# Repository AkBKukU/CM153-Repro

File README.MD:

# Philips CM-153 LMSI Reproduction Card

This project aims to reproduce the LMSI CM-153 card needed to operate a Philips CM-100 CD-ROM drive. This drive was originally released in 1985 and used an early version of the LSMI protocol to connect. Later versions of LMSI cards, such as the CM-260, are not compatible with earlier drives (I do not know what the exact compatibilities are). So an early card is required. The CM-153 is a very uncommon part to find due to it's limited use, high cost, and the fact that it would probably be tossed out with the computer when upgraded being separated from its original drive.

Thanks to Roland who has a [working CM-100 and CM-153](https://www.youtube.com/watch?v=fj-uSWg0LOY) we have some pretty high quality reference images of what this card looks like. It uses all off the shelf 74 series logic chips and one 8251A UART controller. It should therefore be possible to recreate without needing any rare chips or ROM dumps.

## Current Status

The card has been fully reverse engineered and tested to be functional. It has been demonstrated to work using [this](http://mpolibbs.steptail.com/hardware/CDROM/PHILIPS/CM50DRV.ZIP) driver with a CM100 drive.

## Notes

A more acurate build will put 7121 in a socket as it must be removed to use the card with an internal drive. If you just want to use it with an external drive this can be ommited.

The selected DB-15 connector doesn't include the screw nuts which can be purchased separately.

## Parts List

*(Parts picked on 2022-09-07 and reflected best available stock)*

|RefDes|Original Part Number| Datasheet| Digikey Part| Mouser Part|
--- | --- | ---| ---| ---|
|7101|PC74HCT245P|[Datasheet](https://assets.nexperia.com/documents/data-sheet/74HC_HCT245.pdf)|[CD74HCT245E](https://www.digikey.com/en/products/detail/texas-instruments/CD74HCT245E/38454)|[SN74HCT245NE4](https://www.mouser.com/ProductDetail/Texas-Instruments/SN74HCT245NE4?qs=SL3LIuy2dWzrNeCJprt44g%3D%3D)|
|7102|PC74HCT244P|[Datasheet](https://assets.nexperia.com/documents/data-sheet/74HC_HCT244.pdf)|[CD74HCT244E](https://www.digikey.com/en/products/detail/texas-instruments/CD74HCT244E/38450)|[CD74HCT244E](https://www.mouser.com/ProductDetail/Texas-Instruments/CD74HCT244E?qs=Zu35EjizYSQlHH5t78bA9Q%3D%3D)|
|7104,7105|PC74HCT138P|[Datasheet](https://archive.org/details/74HCT138)|[CD74HCT138E](https://www.digikey.com/en/products/detail/texas-instruments/CD74HCT138E/38262)|[CD74HCT138E](https://www.mouser.com/ProductDetail/Texas-Instruments/CD74HCT138E?qs=IEl3ej0IqwCH%2FZM9hy22Dg%3D%3D)|
|7106|PC74HC08P|[Datasheet](https://archive.org/details/manuallib-id-2654066)|[TC74HC08APF](https://www.digikey.com/en/products/detail/toshiba-semiconductor-and-storage/TC74HC08APF/870461)|[SN74HC08AN](https://www.mouser.com/ProductDetail/Texas-Instruments/SN74HC08AN?qs=byeeYqUIh0O9MyGywGYg%252Bw%3D%3D)|
|7107,7108|PC74HC32P|[Datasheet](https://assets.nexperia.com/documents/data-sheet/74HC_HCT32.pdf)|**!M!**[NTE74HC32](https://www.digikey.com/en/products/detail/nte-electronics-inc/NTE74HC32/11650138)|[SN74HC32N](https://www.mouser.com/ProductDetail/Texas-Instruments/SN74HC32N?qs=tJ5HNKWh3OWs99bm2e8RtQ%3D%3D)|
|7109|PC74HC368P|[Datasheet](https://assets.nexperia.com/documents/data-sheet/74HC_HCT368.pdf)|[SN74HC368N](https://www.digikey.com/en/products/detail/texas-instruments/SN74HC368N/376786)|[SN74HC368N](https://www.mouser.com/ProductDetail/Texas-Instruments/SN74HC368N?qs=7KMwW2o1%252BmQFMEJMMaje4Q%3D%3D)|
|7110|PC74HC04P|[Datasheet](https://assets.nexperia.com/documents/data-sheet/74HC_HCT04.pdf)|[SN74HC04N](https://www.digikey.com/en/products/detail/texas-instruments/SN74HC04N/277212)|[SN74HC04AN](https://www.mouser.com/ProductDetail/Texas-Instruments/SN74HC04AN?qs=byeeYqUIh0N6S9uYkR6RCw%3D%3D)|
|7111|PC74HC125P|[Datasheet](https://assets.nexperia.com/documents/data-sheet/74HC_HCT125.pdf)|[CD74HC125E](https://www.digikey.com/en/products/detail/texas-instruments/CD74HC125E/475901)|[SN74HC125NE4](https://www.mouser.com/ProductDetail/Texas-Instruments/SN74HC125NE4?qs=AgY10sKTvDLokkOrwnzHmA%3D%3D)|
|7112,7113|PC74HC74P|[Datasheet](https://assets.nexperia.com/documents/data-sheet/74HC_HCT74.pdf)|NOT AVAILABLE|[CD74HC74EE4](https://www.mouser.com/ProductDetail/Texas-Instruments/CD74HC74EE4?qs=xFfolx0DHx2A6AZK2ZbvuQ%3D%3D)|
|7114,7115|PC74HC4024P|[Datasheet](https://assets.nexperia.com/documents/data-sheet/74HC4024.pdf)|[CD74HC4024E](https://www.digikey.com/en/products/detail/texas-instruments/CD74HC4024E/376737)|[CD74HC4024E](https://www.mouser.com/ProductDetail/Texas-Instruments/CD74HC4024E?qs=pt%2FIv5r0EPeVxf9RvRS8Kg%3D%3D)|
|7116,7117,7118|MC74HC595AN|[Datasheet](https://assets.nexperia.com/documents/data-sheet/74HC_HCT595.pdf)|[CD74HC595E](https://www.digikey.com/en/products/detail/texas-instruments/CD74HC595E/1507396)|[SN74HC595NE4](https://www.mouser.com/ProductDetail/Texas-Instruments/SN74HC595NE4?qs=AgY10sKTvDK0jki9CKjSwg%3D%3D)|
|7119|P8251A|[Datasheet](http://map.grauw.nl/resources/midi/intel_8251.pdf)|NOT AVAILABLE|NOT AVAILABLE|
|7120|DS26LS31CN|[Datasheet](https://www.ti.com/lit/ds/symlink/am26ls31.pdf)|NOT AVAILABLE|[AM26LS31CN](https://www.mouser.com/ProductDetail/Texas-Instruments/AM26LS31CN?qs=mTHRaKC2c7NO%252BlWH6D4lHg%3D%3D)|
|7121|DS26LS32CN|[Datasheet](https://www.ti.com/lit/ds/symlink/am26ls32am.pdf)|[AM26LS32ACN](https://www.digikey.com/en/products/detail/texas-instruments/AM26LS32ACN/277026)|[AM26LS32ACN](https://www.mouser.com/ProductDetail/Texas-Instruments/AM26LS32ACN?qs=IF4wzcbwb3oK65Lb3k1iHg%3D%3D)|
|X-TAL|4.9152MHz||[MP042](https://www.digikey.com/en/products/detail/cts-frequency-controls/MP042/67676)|[MP042](https://www.mouser.com/ProductDetail/CTS-Electronic-Components/MP042?qs=Mr%252BgrRYddfqYTabPpjTZhQ%3D%3D)|
|Big cap (C9)|50V 10uF||[ECA-1HHG100B](https://www.digikey.com/en/products/detail/panasonic-electronic-components/ECA-1HHG100B/413608)|[ECA-1HHG100B](https://www.mouser.com/ProductDetail/Panasonic/ECA-1HHG100B?qs=86KMePBwEH3eLbQCzM6gng%3D%3D)|
|X5|2x8 pin IDC||2x [826656-2](https://www.digikey.com/en/products/detail/te-connectivity-amp-connectors/826656-2/2276228)|2x [826656-2](https://www.mouser.com/ProductDetail/TE-Connectivity/826656-2?qs=DbJIyW2JsP7yZR%252BsE22lHg%3D%3D)|
|X2|2x4 pin IDC||[826656-2](https://www.digikey.com/en/products/detail/te-connectivity-amp-connectors/826656-2/2276228)|[826656-2](https://www.mouser.com/ProductDetail/TE-Connectivity/826656-2?qs=DbJIyW2JsP7yZR%252BsE22lHg%3D%3D)|
|Y3|15 pin D-Sub||[D15S13B4GX00LF](https://www.digikey.com/en/products/detail/amphenol-cs-fci/D15S13B4GX00LF/1539503)|[D15S13B4GX00LF](https://www.mouser.com/ProductDetail/Amphenol-FCI/D15S13B4GX00LF?qs=V0y2QjpmBGTkGk8fxG40%2FA%3D%3D)|
|C1, C2, C3, C8|100nF||[C1206C104K5RAC7800](https://www.digikey.com/en/products/detail/kemet/C1206C104K5RAC7800/411248)|[C1206C104K5RAC](https://www.mouser.com/ProductDetail/KEMET/C1206C104K5RAC?qs=utjsALNw%2FXTrbYrRGHNW%2Fw%3D%3D)|
|C4|33pF||[885012008020](https://www.digikey.com/en/products/detail/w%C3%BCrth-elektronik/885012008020/5453728)|[885012008020](https://www.mouser.com/ProductDetail/Wurth-Elektronik/885012008020?qs=0KOYDY2FL291ofVgKwDyIQ%3D%3D)|
|C5, C6|14pF||[885012008038](https://www.digikey.com/en/products/detail/w%C3%BCrth-elektronik/885012008038/5453737)|[885012008038](https://www.mouser.com/ProductDetail/Wurth-Elektronik/885012008038?qs=0KOYDY2FL2%252BQ%252BIYq9i7pEA%3D%3D)|
|C7|47pF||[885012008021](https://www.digikey.com/en/products/detail/w%C3%BCrth-elektronik/885012008021/5453729)|[885012008021](https://www.mouser.com/ProductDetail/Wurth-Elektronik/885012008021?qs=0KOYDY2FL2%2F%252Bm93ZHe2ewg%3D%3D)|
|R1|10KΩ||[RMCF1206JT10K0](https://www.digikey.com/en/products/detail/stackpole-electronics-inc/RMCF1206JT10K0/1757427)|[RC1206FR-1310KL](https://www.mouser.com/ProductDetail/YAGEO/RC1206FR-1310KL?qs=sGAEpiMZZMvdGkrng054t8AJgcdMkx7xV9EP%2FUfQrjQ%3D)|
|R2|1MΩ||[HV73V2BTTD105J](https://www.digikey.com/en/products/detail/koa-speer-electronics-inc/HV73V2BTTD105J/11495356)|[RC1206JR-071ML](https://www.mouser.com/ProductDetail/YAGEO/RC1206JR-071ML?qs=sGAEpiMZZMvdGkrng054t8Tx25L%252BvTaRR%252BfTyDGULRs%3D)|
|R3|100Ω||[RNCP1206FTD100R](https://www.digikey.com/en/products/detail/stackpole-electronics-inc/RNCP1206FTD100R/2240316)|[RC1206JR-07100RL](https://www.mouser.com/ProductDetail/YAGEO/RC1206JR-07100RL?qs=sGAEpiMZZMvdGkrng054t8Tx25L%252BvTaRBgLzIJA%2FMIc%3D)|
|R4|1KΩ||[RMCF1206JT1K00](https://www.digikey.com/en/products/detail/stackpole-electronics-inc/RMCF1206JT1K00/1757526)|[RC1206FR-131KL](https://www.mouser.com/ProductDetail/YAGEO/RC1206FR-131KL?qs=sGAEpiMZZMvdGkrng054t8AJgcdMkx7xEX6WAGFcbHI%3D)|
|R5, R6, R7, R8|120Ω||[RMCF1206JT120R](https://www.digikey.com/en/products/detail/stackpole-electronics-inc/RMCF1206JT120R/1757405)|[RC1206FR-07120RL](https://www.mouser.com/ProductDetail/YAGEO/RC1206FR-07120RL?qs=sGAEpiMZZMvdGkrng054t8AJgcdMkx7xHngnO2SPVlk%3D)|
|R10, R12, R14, R16|270Ω||[MCR18ERTJ271](https://www.digikey.com/en/products/detail/rohm-semiconductor/MCR18ERTJ271/2796388)|[RC1206FR-07270RL](https://www.mouser.com/ProductDetail/YAGEO/RC1206FR-07270RL?qs=sGAEpiMZZMvdGkrng054t8AJgcdMkx7xeAVb6tXWI0g%3D)|
|R9, R11, R13, R15|220Ω||[RMCF1206JT220R](https://www.digikey.com/en/products/detail/stackpole-electronics-inc/RMCF1206JT220R/1757377)|[AC1206JR-07220RL](https://www.mouser.com/ProductDetail/YAGEO/AC1206JR-07220RL?qs=sGAEpiMZZMvdGkrng054t7zOzNqIRvGc5GFE1pYUTcM%3D)|
|Card Bracket|Bottom DB15 Cutout||[9200-11](https://www.digikey.com/en/products/detail/keystone-electronics/9200-11/2746684)|[9200-11](https://www.mouser.com/ProductDetail/Keystone-Electronics/9200-11?qs=%252BU2dxLPlMC0AIccOWCwv6Q%3D%3D)|

*All SMD parts 1206 size.*

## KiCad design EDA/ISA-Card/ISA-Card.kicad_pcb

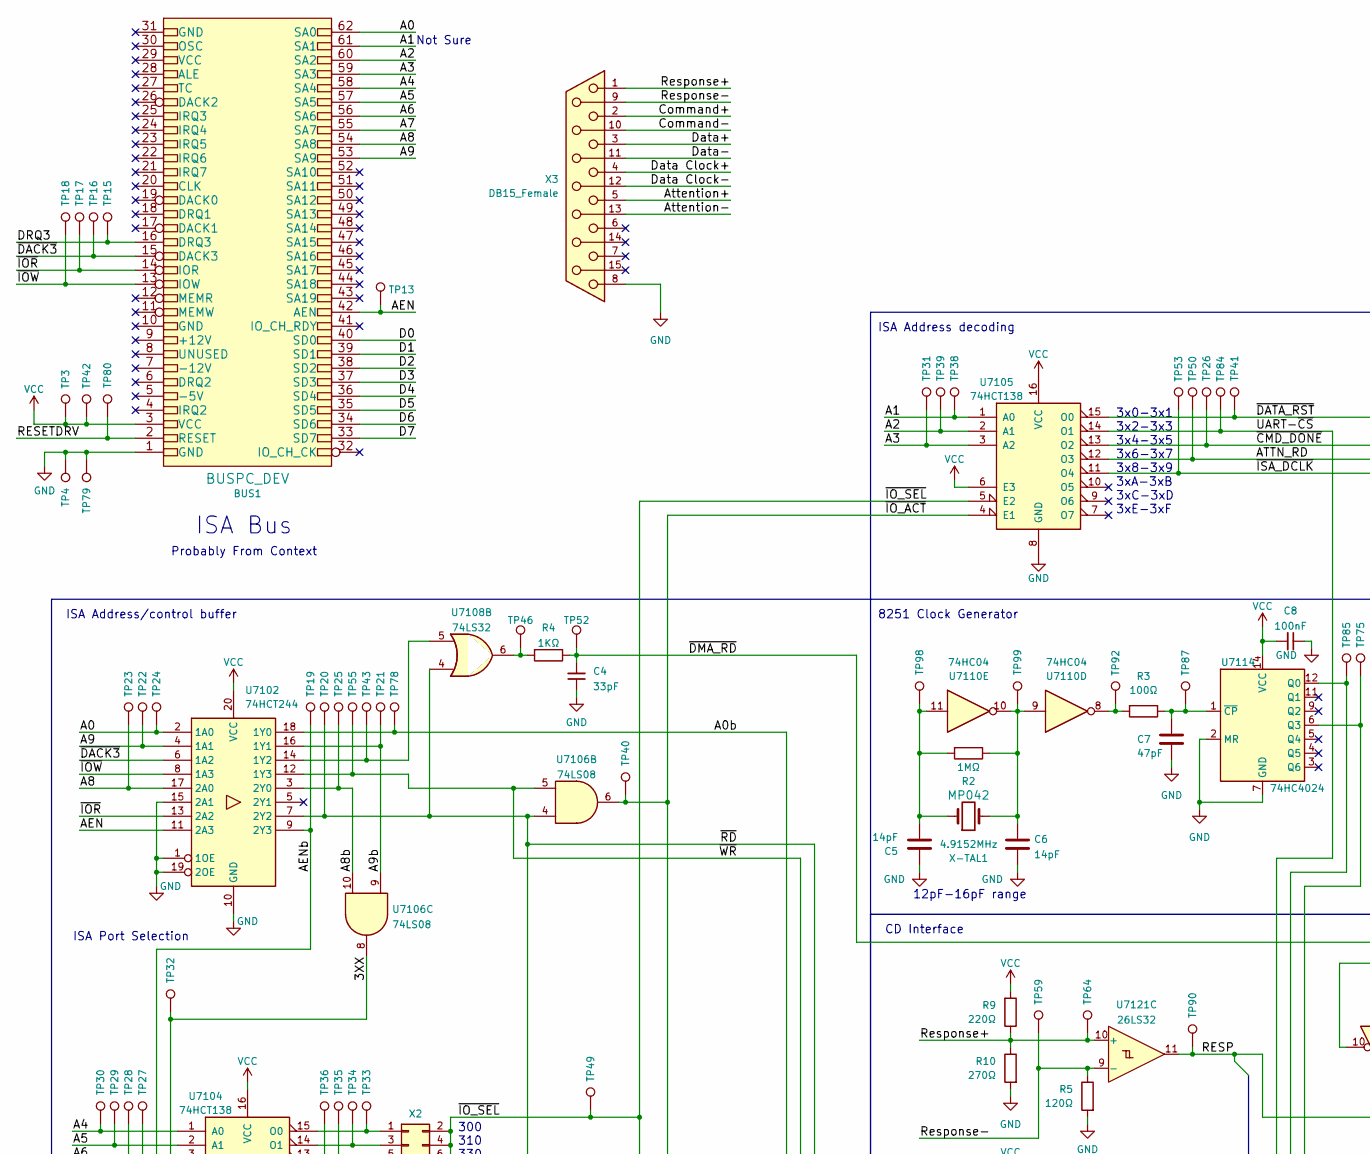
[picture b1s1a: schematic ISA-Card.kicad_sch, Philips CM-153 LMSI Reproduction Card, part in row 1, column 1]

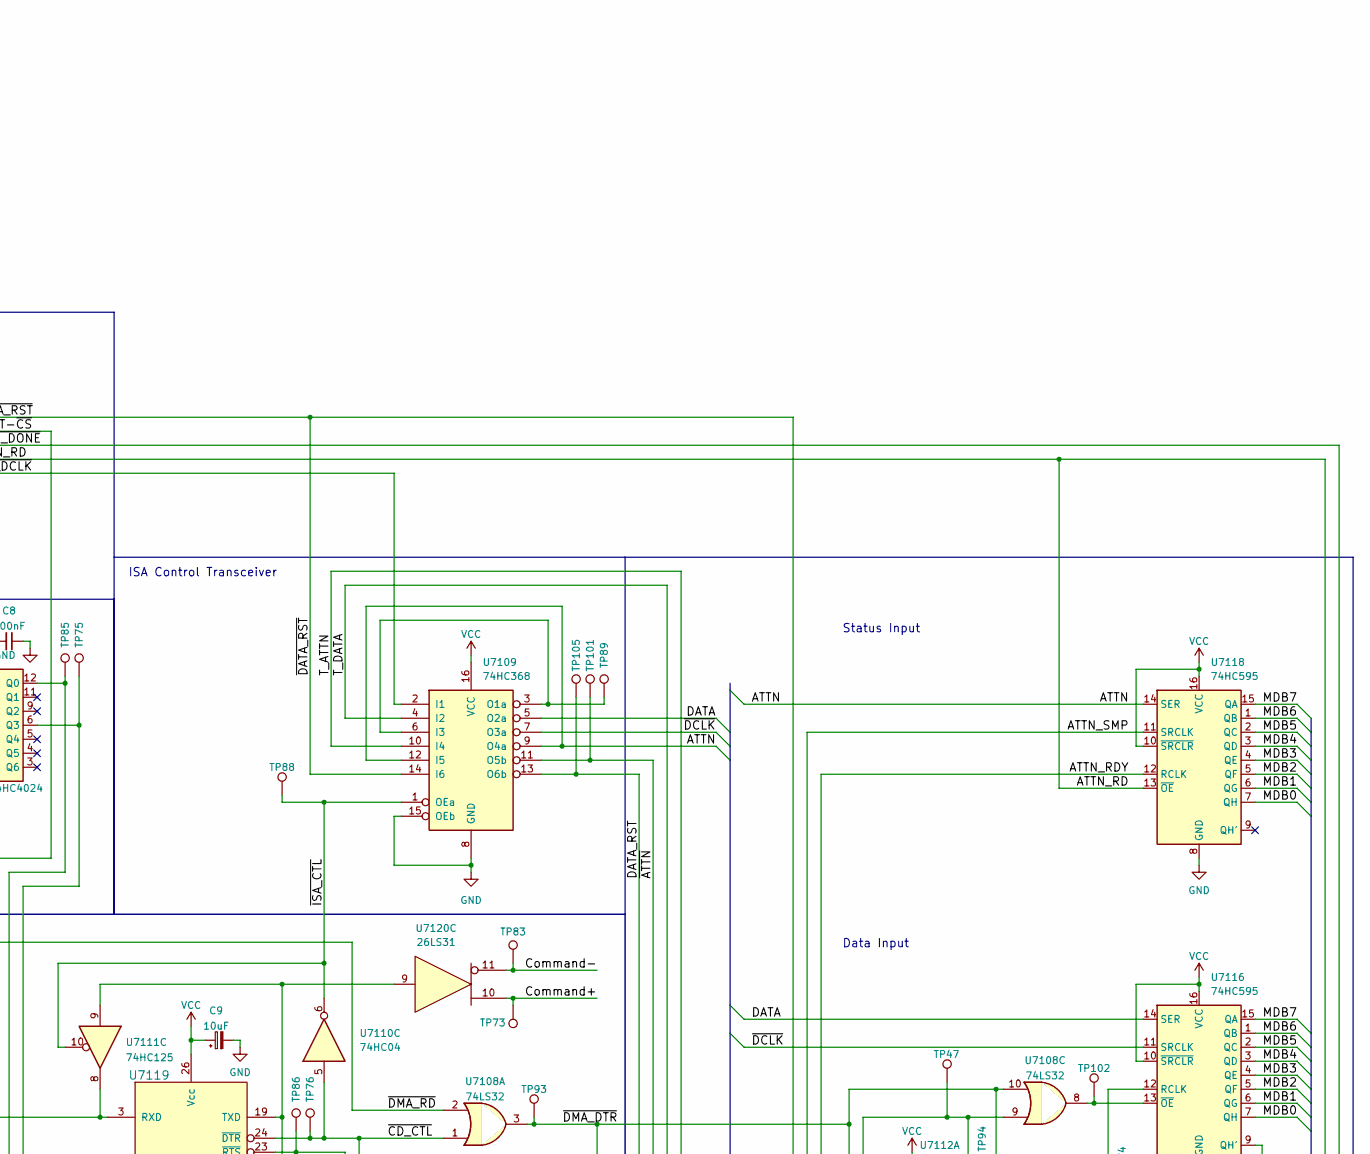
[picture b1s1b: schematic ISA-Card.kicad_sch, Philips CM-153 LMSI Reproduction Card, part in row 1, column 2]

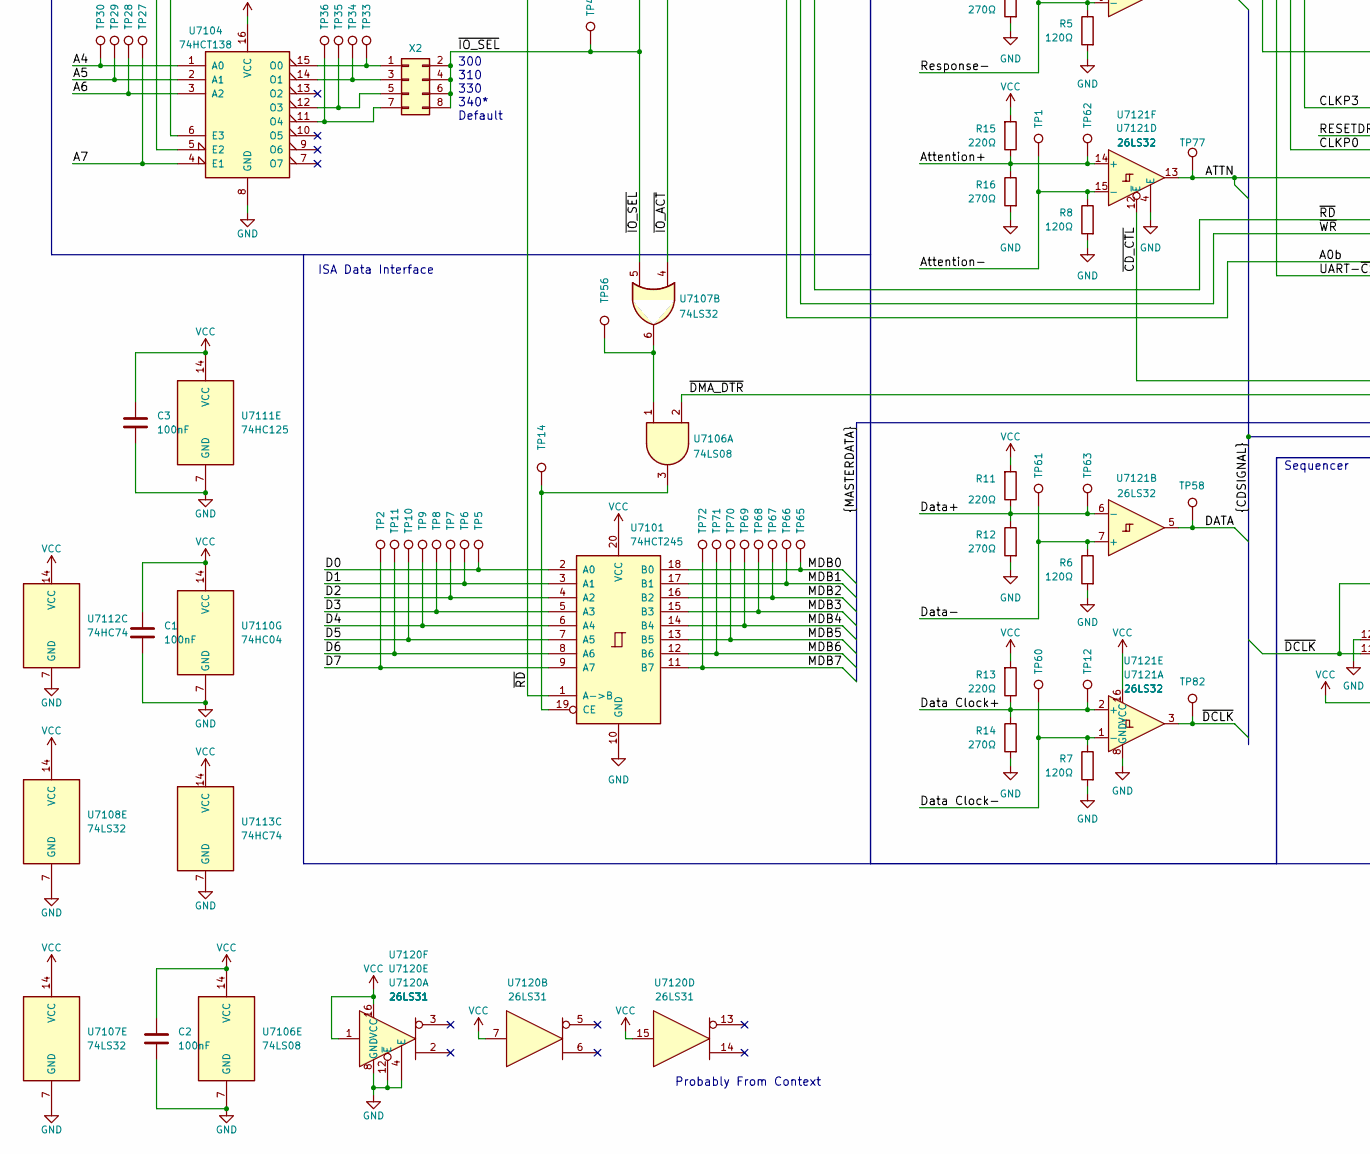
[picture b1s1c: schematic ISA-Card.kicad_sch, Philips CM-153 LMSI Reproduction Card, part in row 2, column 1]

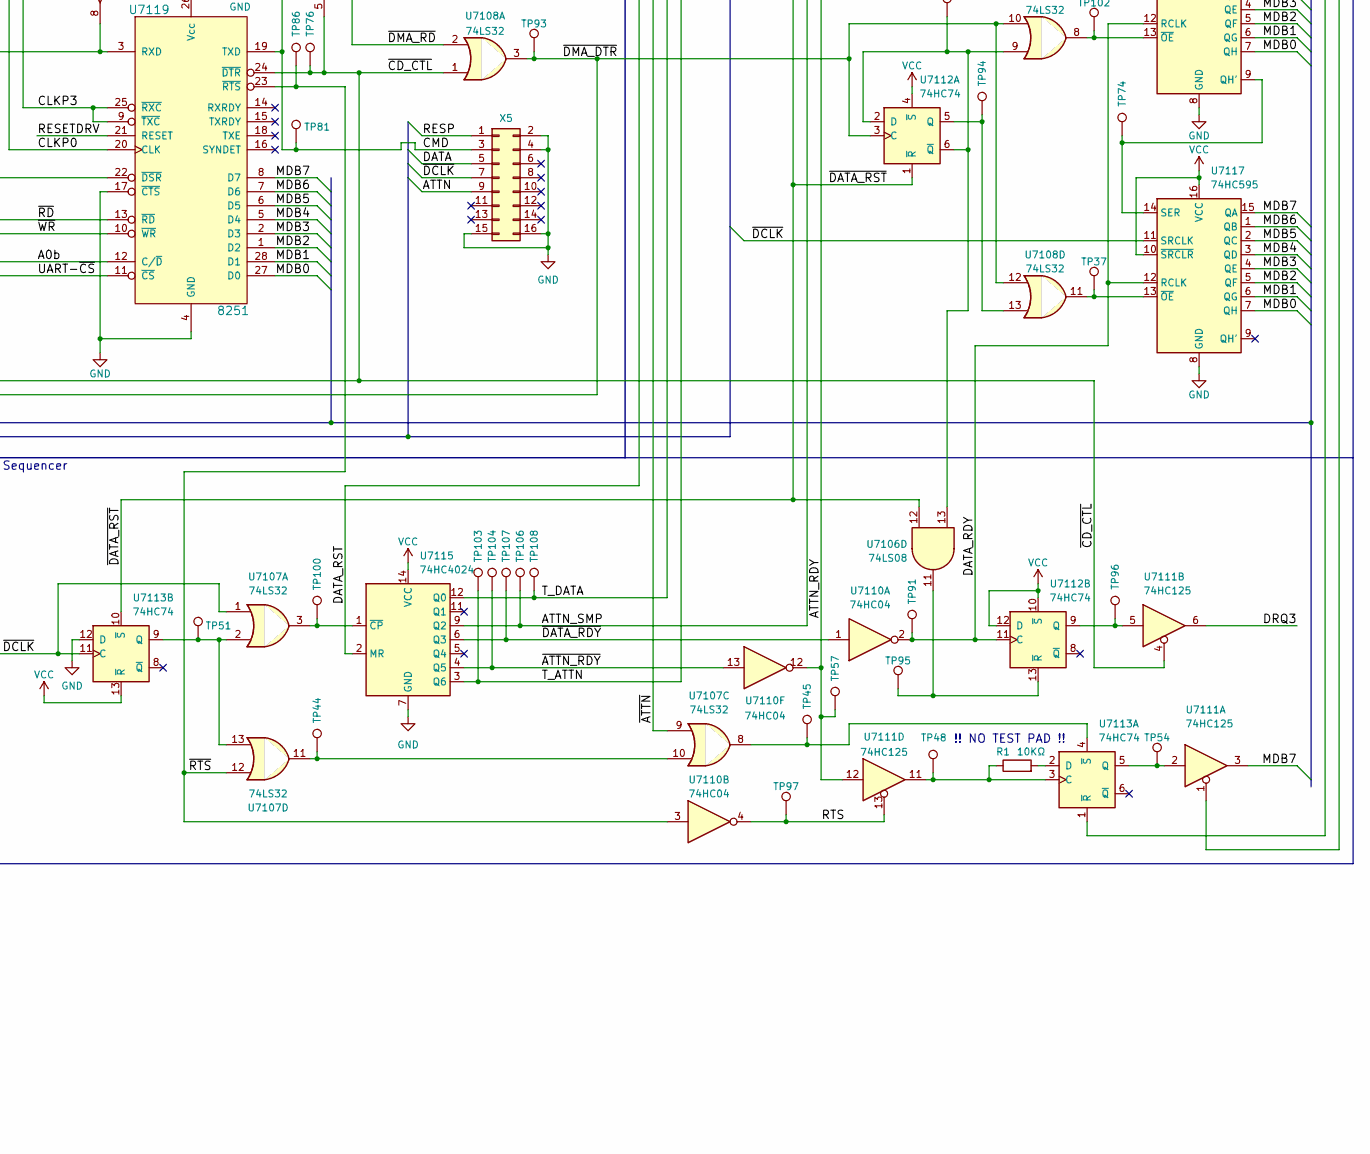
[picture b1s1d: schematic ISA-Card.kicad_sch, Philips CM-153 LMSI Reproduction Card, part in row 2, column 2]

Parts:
BUS1: BUSPC_DEV; Conn_Edge_PCB_ISA8
C1, C2, C3, C8: 100nF; C_1206_3216Metric
C4: 33pF; C_1206_3216Metric
C5, C6: 14pF; C_1206_3216Metric
C7: 47pF; C_1206_3216Metric
C9: 10uF; CP_Radial_D10.0mm_P5.00mm
R1: 10KΩ; R_1206_3216Metric
R2: 1MΩ; R_1206_3216Metric
R3: 100Ω; R_1206_3216Metric
R4: 1KΩ; R_1206_3216Metric
R5, R6, R7, R8: 120Ω; R_1206_3216Metric
R9, R11, R13, R15: 220Ω; R_1206_3216Metric
R10, R12, R14, R16: 270Ω; R_1206_3216Metric
TP1, TP2, TP3, TP4, TP5, TP6, TP7, TP8, TP9, TP10, TP11, TP12, TP13, TP14, TP15, TP16, TP17, TP18, TP19, TP20, TP21, TP22, TP23, TP24, TP25, TP26, TP27, TP28, TP29, TP30, TP31, TP32, TP33, TP34, TP35, TP36, TP37, TP38, TP39, TP40, TP41, TP42, TP43, TP44, TP45, TP46, TP47, TP48, TP49, TP50, TP51, TP52, TP53, TP54, TP55, TP56, TP57, TP58, TP59, TP60, TP61, TP62, TP63, TP64, TP65, TP66, TP67, TP68, TP69, TP70, TP71, TP72, TP73, TP74, TP75, TP76, TP77, TP78, TP79, TP80, TP81, TP82, TP83, TP84, TP85, TP86, TP87, TP88, TP89, TP90, TP91, TP92, TP93, TP94, TP95, TP96, TP97, TP98, TP99, TP100, TP101, TP102, TP103, TP104, TP105, TP106, TP107, TP108: TestPoint; Test Point
U7101: 74HCT245; DIP-20_W7.62mm
U7102: 74HCT244; DIP-20_W7.62mm
U7104, U7105: 74HCT138; DIP-16-Plain
U7106: 74LS08; DIP-14-Plain
U7107, U7108: 74LS32; DIP-14-Plain
U7109: 74HC368; DIP-16-Plain
U7110: 74HC04; DIP-14-Plain
U7111: 74HC125; DIP-14-Plain
U7112, U7113: 74HC74; DIP-14-Plain
U7114, U7115: 74HC4024; DIP-14-Plain
U7116, U7117, U7118: 74HC595; DIP-16-Plain
U7119: 8251; DIP-28_W15.24mm
U7120: 26LS31
U7121: 26LS32
X2: Conn_02x04_Counter_Clockwise; PinHeader_2x04_P2.54mm_Vertical
X3: DB15_Female; DSUB-15_Female_Horizontal_P2.77x2.84mm_EdgePinOffset7.70mm_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
X5: Conn_02x08_Counter_Clockwise; PinHeader_2x08_P2.54mm_Vertical
X-TAL1: 4.9152MHz; Crystal_HC49-U_Horizontal; Part Number MP042

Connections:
/3XX: TP32.1, U7104.6 (E3), U7106.8
/A0: BUS1.62 (SA0), TP24.1, U7102.2 (1A0)
/A0b: TP78.1, U7102.18 (1Y0), U7119.12 (C/~D)
/A1: BUS1.61 (SA1), TP38.1, U7105.1 (A0)
/A2: BUS1.60 (SA2), TP39.1, U7105.2 (A1)
/A3: BUS1.59 (SA3), TP31.1, U7105.3 (A2)
/A4: BUS1.58 (SA4), TP30.1, U7104.1 (A0)
/A5: BUS1.57 (SA5), TP29.1, U7104.2 (A1)
/A6: BUS1.56 (SA6), TP28.1, U7104.3 (A2)
/A7: BUS1.55 (SA7), TP27.1, U7104.4 (E1)
/A8: BUS1.54 (SA8), TP23.1, U7102.17 (2A0)
/A8b: TP25.1, U7102.3 (2Y0), U7106.10
/A9: BUS1.53 (SA9), TP22.1, U7102.4 (1A1)
/A9b: TP21.1, U7102.16 (1Y1), U7106.9
/AEN: BUS1.42 (AEN), TP13.1, U7102.11 (2A3)
/AENb: TP19.1, U7102.9 (2Y3), U7104.5 (E2)
/ATTN: TP77.1, U7109.9 (O4a), U7109.12 (I5), U7118.14 (SER), U7119.22 (~DSR), U7121.13, X5.9
/ATTN_RD: TP50.1, U7105.12 (O3), U7113.1 (~R), U7118.13 (~OE)
/ATTN_RDY: TP57.1, U7110.12, U7111.12, U7118.12 (RCLK)
/ATTN_SMP: TP106.1, U7115.9 (Q2), U7118.11 (SRCLK)
/ATTNb: TP101.1, U7107.9, U7109.11 (O5b)
/Attention+: R15.1, R16.1, TP62.1, U7121.14 (+), X3.5
/Attention-: R8.1, TP1.1, U7121.15 (-), X3.13
/CLKP0: TP85.1, U7114.12 (Q0), U7119.20 (CLK)
/CLKP3: TP75.1, U7114.6 (Q3), U7119.9 (~TXC), U7119.25 (~RXC)
/CMD: TP81.1, U7111.9, U7119.19 (TXD), U7120.9, X5.3
/Command+: TP73.1, U7120.10, X3.2
/Command-: TP83.1, U7120.11, X3.10
/D0: BUS1.40 (SD0), TP5.1, U7101.2 (A0)
/D1: BUS1.39 (SD1), TP6.1, U7101.3 (A1)
/D2: BUS1.38 (SD2), TP7.1, U7101.4 (A2)
/D3: BUS1.37 (SD3), TP8.1, U7101.5 (A3)
/D4: BUS1.36 (SD4), TP9.1, U7101.6 (A4)
/D5: BUS1.35 (SD5), TP10.1, U7101.7 (A5)
/D6: BUS1.34 (SD6), TP11.1, U7101.8 (A6)
/D7: BUS1.33 (SD7), TP2.1, U7101.9 (A7)
/DATA: TP58.1, U7109.5 (O2a), U7116.14 (SER), U7121.5, X5.5
/DATA_RDY: TP91.1, U7110.2, U7112.11 (C), U7116.12 (RCLK), U7117.12 (RCLK)
/DCLK: TP82.1, U7107.1, U7109.7 (O3a), U7113.11 (C), U7116.11 (SRCLK), U7117.11 (SRCLK), U7121.3, X5.7
/DRQ3: BUS1.16 (DRQ3), TP15.1, U7111.6
/Data Clock+: R13.1, R14.1, TP12.1, U7121.2 (+), X3.4
/Data Clock-: R7.1, TP60.1, U7121.1 (-), X3.12
/Data+: R11.1, R12.1, TP63.1, U7121.6 (-), X3.3
/Data-: R6.1, TP61.1, U7121.7 (+), X3.11 (P111)
/ISA_DCLK: TP53.1, U7105.11 (O4), U7109.2 (I1)
/MDB0: TP65.1, U7101.18 (B0), U7116.7 (QH), U7117.7 (QH), U7118.7 (QH), U7119.27 (D0)
/MDB1: TP66.1, U7101.17 (B1), U7116.6 (QG), U7117.6 (QG), U7118.6 (QG), U7119.28 (D1)
/MDB2: TP67.1, U7101.16 (B2), U7116.5 (QF), U7117.5 (QF), U7118.5 (QF), U7119.1 (D2)
/MDB3: TP68.1, U7101.15 (B3), U7116.4 (QE), U7117.4 (QE), U7118.4 (QE), U7119.2 (D3)
/MDB4: TP69.1, U7101.14 (B4), U7116.3 (QD), U7117.3 (QD), U7118.3 (QD), U7119.5 (D4)
/MDB5: TP70.1, U7101.13 (B5), U7116.2 (QC), U7117.2 (QC), U7118.2 (QC), U7119.6 (D5)
/MDB6: TP71.1, U7101.12 (B6), U7116.1 (QB), U7117.1 (QB), U7118.1 (QB), U7119.7 (D6)
/MDB7: TP72.1, U7101.11 (B7), U7111.3, U7116.15 (QA), U7117.15 (QA), U7118.15 (QA), U7119.8 (D7)
/RESETDRV: BUS1.2 (RESET), TP80.1, U7119.21 (RESET)
/RESP: TP90.1, U7111.8, U7119.3 (RXD), U7121.11, X5.1
/RTS: TP97.1, U7110.4, U7111.13
/Response+: R9.1, R10.1, TP64.1, U7121.10 (+), X3.1
/Response-: R5.1, TP59.1, U7121.9 (-), X3.9
/T_ATTN: TP103.1, U7109.10 (I4), U7115.3 (Q6)
/T_DATA: TP108.1, U7109.4 (I2), U7115.12 (Q0)
/UART-~CS: TP84.1, U7105.14 (O1), U7119.11 (~CS)
/~ATTN_RDY: TP104.1, U7110.13, U7115.4 (Q5)
/~CD_CTL: TP76.1, U7108.1, U7110.5, U7111.4, U7119.24 (~DTR), U7121.12 (~E)
/~CMD_DONE: TP26.1, U7105.13 (O2), U7111.1
/~DACK3: BUS1.15 (DACK3), TP16.1, U7102.6 (1A2)
/~DATA_RDY: TP107.1, U7110.1, U7115.6 (Q3)
/~DMA_DTR: TP93.1, U7106.2, U7108.3, U7108.10, U7108.12, U7112.3 (C)
/~DMA_RD: C4.2, R4.1, TP52.1, U7108.2
/~IOR: BUS1.14 (IOR), TP17.1, U7102.13 (2A2)
/~IOW: BUS1.13 (IOW), TP18.1, U7102.8 (1A3)
/~IO_ACT: TP40.1, U7105.4 (E1), U7106.6, U7107.4
/~IO_SEL: TP49.1, U7105.5 (E2), U7107.5, X2.2, X2.4, X2.6, X2.8
/~ISA_CTL: TP88.1, U7109.1 (OEa), U7110.6, U7111.10
/~LOAD_CMD_DLY: TP105.1, U7109.13 (O6b), U7115.2 (MR)
/~LOAD_CMD: TP41.1, U7105.15 (O0), U7106.12, U7109.14 (I6), U7112.1 (~R), U7113.10 (~S)
/~RD: TP20.1, U7101.1 (A->B), U7102.7 (2Y2), U7106.4, U7108.4, U7119.13 (~RD)
/~RTS: TP86.1, U7107.12, U7110.3, U7119.23 (~RTS)
/~WR: TP55.1, U7102.12 (1Y3), U7106.5, U7119.10 (~WR)
GND: BUS1.1 (GND), C1.2, C2.2, C3.2, C4.1, C5.1, C6.1, C7.2, C8.1, C9.2, R5.2, R6.2, R7.2, R8.2, R10.2, R12.2, R14.2, R16.2, TP4.1, TP79.1, U7101.10 (GND), U7102.1 (1OE), U7102.10 (GND), U7102.15 (2A1), U7102.19 (2OE), U7104.8 (GND), U7105.8 (GND), U7106.7 (GND), U7107.7 (GND), U7108.7 (GND), U7109.8 (GND), U7109.15 (OEb), U7110.7 (GND), U7111.7 (GND), U7112.7 (GND), U7113.7 (GND), U7113.12 (D), U7114.2 (MR), U7114.7 (GND), U7115.7 (GND), U7116.8 (GND), U7117.8 (GND), U7118.8 (GND), U7119.4 (GND), U7119.17 (~CTS), U7120.4 (E), U7120.8 (GND), U7120.12 (~E), U7121.4 (E), U7121.8 (GND), X3.8, X5.2, X5.4, X5.15, X5.16
unnamed: C5.2, R2.2, TP98.1, U7110.11, X-TAL1.1
unnamed: C6.2, R2.1, TP99.1, U7110.9, U7110.10, X-TAL1.2
unnamed: C7.1, R3.1, TP87.1, U7114.1 (~CP)
unnamed: R1.1, TP48.1, U7111.11, U7113.3 (C)
unnamed: R1.2, U7113.2 (D)
unnamed: R3.2, TP92.1, U7110.8
unnamed: R4.2, TP46.1, U7108.6
unnamed: TP14.1, U7101.19 (CE), U7106.3
unnamed: TP33.1, U7104.15 (O0), X2.1
unnamed: TP34.1, U7104.14 (O1), X2.3
unnamed: TP35.1, U7104.12 (O3), X2.5
unnamed: TP36.1, U7104.11 (O4), X2.7
unnamed: TP43.1, U7102.14 (1Y2), U7108.5
unnamed: TP51.1, U7107.2, U7107.13, U7113.9 (Q)
unnamed: TP54.1, U7111.2, U7113.5 (Q)
unnamed: TP56.1, U7106.1, U7107.6
unnamed: TP89.1, U7109.3 (O1a), U7109.6 (I3)
unnamed: TP96.1, U7111.5, U7112.9 (Q)
unnamed: TP95.1, U7106.11, U7112.13 (~R)
unnamed: TP100.1, U7107.3, U7115.1 (~CP)
unnamed: TP44.1, U7107.10, U7107.11
unnamed: TP47.1, U7106.13, U7108.9, U7112.2 (D), U7112.6 (~Q)
unnamed: TP94.1, U7108.13, U7112.5 (Q)
unnamed: TP45.1, U7107.8, U7113.4 (~S)
unnamed: TP74.1, U7116.9 (QH'), U7117.14 (SER)
unnamed: TP102.1, U7108.8, U7116.13 (~OE)
unnamed: TP37.1, U7108.11, U7117.13 (~OE)
VCC: BUS1.3 (VCC), C1.1, C2.1, C3.1, C8.2, C9.1, R9.2, R11.2, R13.2, R15.2, TP3.1, TP42.1, U7101.20 (VCC), U7102.20 (VCC), U7104.16 (VCC), U7105.6 (E3), U7105.16 (VCC), U7106.14 (VCC), U7107.14 (VCC), U7108.14 (VCC), U7109.16 (VCC), U7110.14 (VCC), U7111.14 (VCC), U7112.4 (~S), U7112.10 (~S), U7112.12 (D), U7112.14 (VCC), U7113.13 (~R), U7113.14 (VCC), U7114.14 (VCC), U7115.14 (VCC), U7116.10 (~SRCLR), U7116.16 (VCC), U7117.10 (~SRCLR), U7117.16 (VCC), U7118.10 (~SRCLR), U7118.16 (VCC), U7119.26 (Vcc), U7120.1, U7120.7, U7120.15, U7120.16 (VCC), U7121.16 (VCC)

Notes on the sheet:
Probably From Context
3x0-3x1 3x2-3x3 3x4-3x5 3x6-3x7 3x8-3x9 3xA-3xB 3xC-3xD 3xE-3xF
12pF-16pF range
!! NO TEST PAD !!
ISA Address/control buffer
Not Sure
ISA Bus
300 310 330 340* Default
ISA Address decoding
Sequencer
Data Input
ISA Control Transceiver
ISA Port Selection
CD Interface
8251 Clock Generator
Status Input
ISA Data Interface

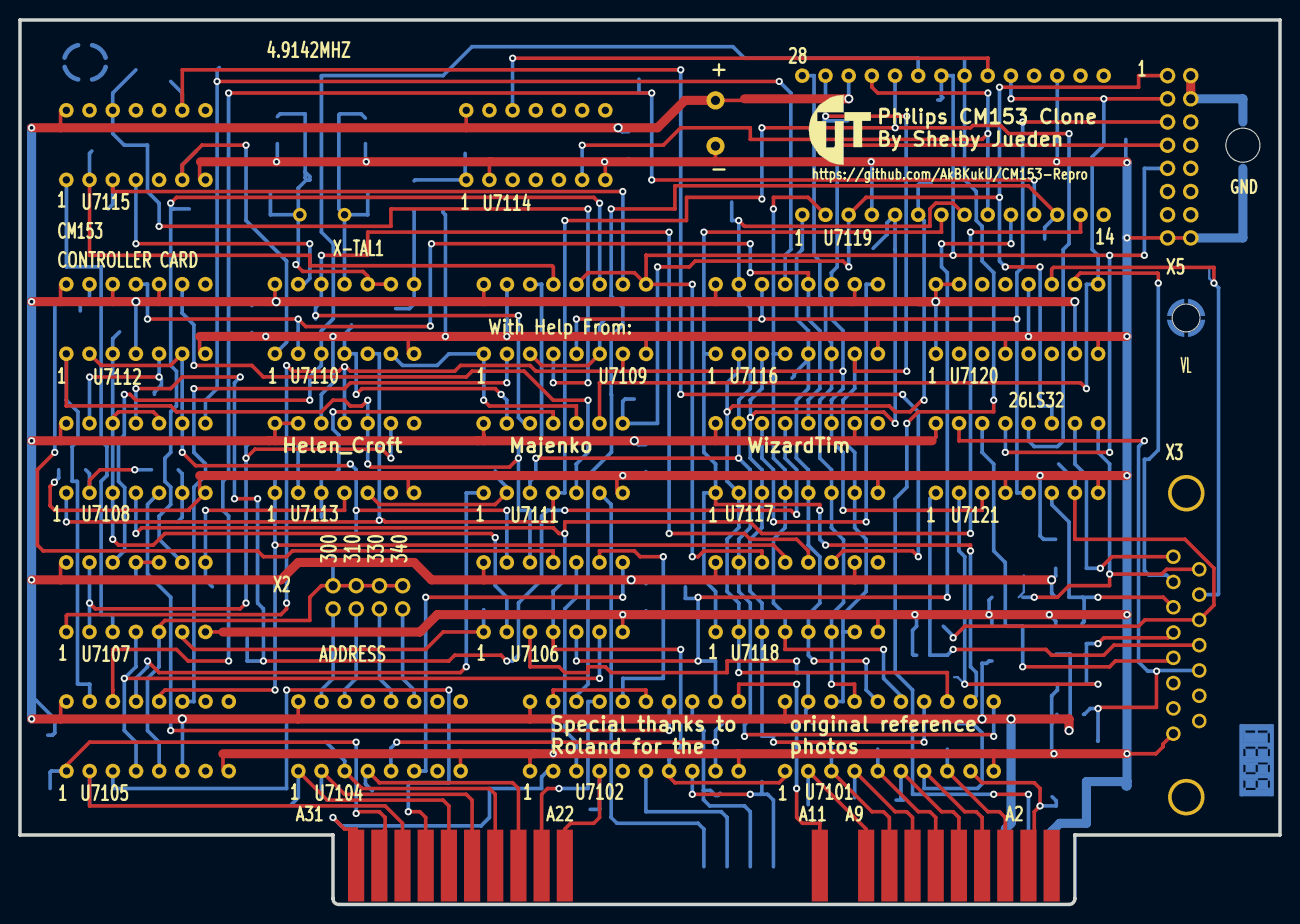
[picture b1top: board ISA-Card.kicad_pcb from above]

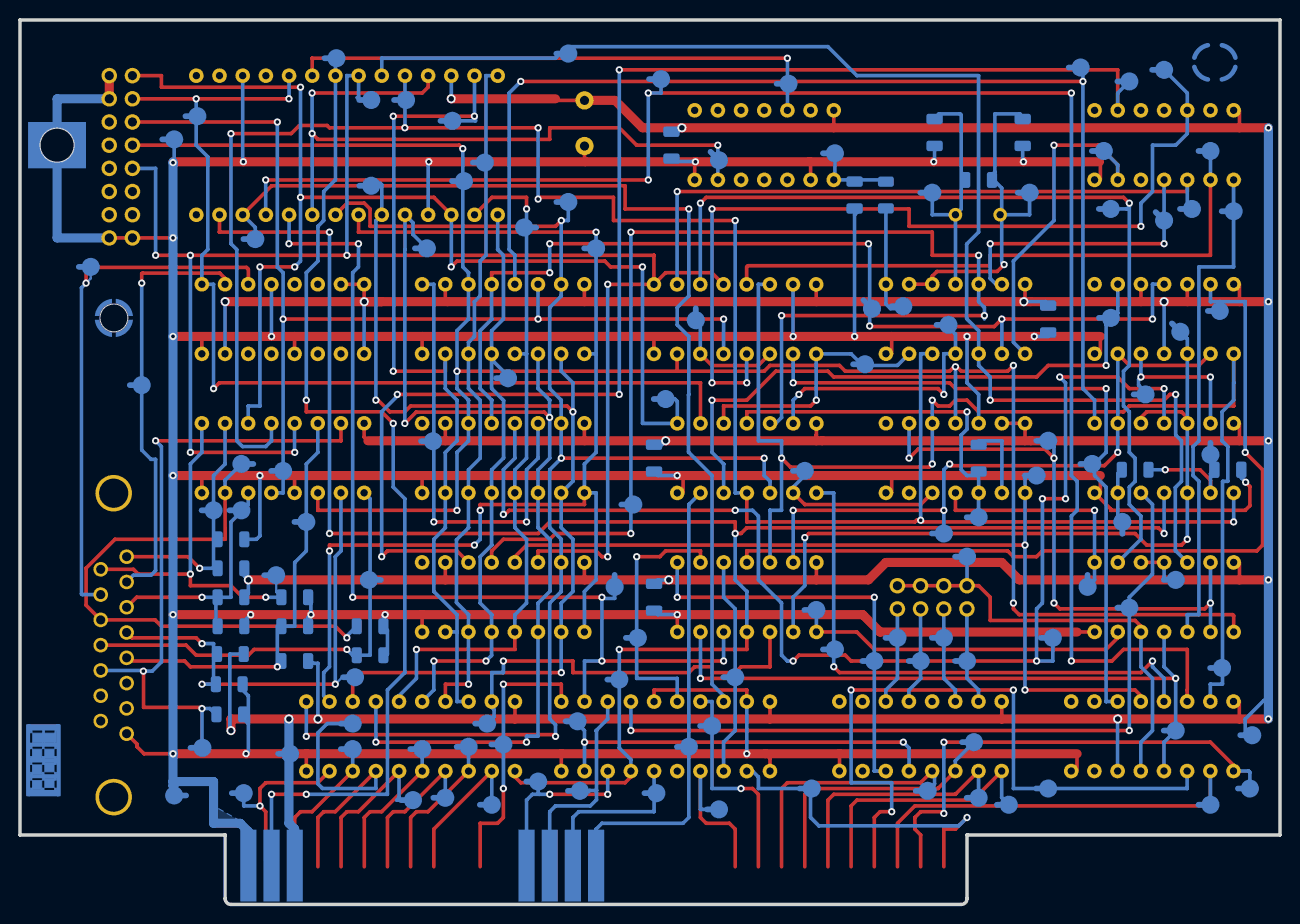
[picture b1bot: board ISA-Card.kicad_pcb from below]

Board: 2 copper layers, 138.0 x 96.9 mm, 158 parts (24 on the bottom side), 107 nets.

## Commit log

2022-08-20 Init
2022-08-20 Add parts
2022-08-20 fix parts
2022-08-20 begining schematic
2022-08-21 more traces
2022-08-21 Label LMSI Connector
2022-08-21 More chips finished
2022-08-26 Expand schematic
2022-08-27 595's done
2022-08-27 1711 finished
2022-08-27 1713 finished
2022-08-27 All but buffer and external connector done
2022-08-27 check in with fault in schematic for internal connector pin 1
2022-08-28 Schematic done except response signal, PCB started
2022-08-28 clean up schematic
2022-08-28 PCB Major Progress
2022-08-28 Add additional PCB image
2022-08-29 PCB Primary Routing finished, except 2 traces
2022-08-29 Update Schematic PDF
2022-08-29 Connect RCLKs together and update doc
2022-08-29 Disconnect RCLKs in favor of different idea
2022-08-29 cleanup
2022-08-29 readd image
2022-08-29 Add more things to check
2022-08-31 Mark default port on schematic
2022-08-31 Added Philips Custom Mounting Holes
2022-08-31 Added test points
2022-08-31 Add schematic pdf
2022-08-31 Bring in schematic changes from Helen Croft
2022-08-31 Fixed missed connection on 7113 Pin 13
2022-08-31 All nets checked and annotated for number of test pads Three nets are missing test pads, though one is connecting a two pins through a resistor and seems harmless. The othersare going to the drive in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
2022-09-01 Add extra silk screen markings, not fully acurate though
2022-09-01 Change unseen traces under UART to connect data clocks and update unsure traces
2022-09-01 Removed unused pads from ISA connector
2022-09-01 Export gerbers and PDF
2022-09-01 Add more schematic cleanup from Helen Croft
2022-09-01 Connect Response to RXD
2022-09-01 Connect buffer enable to DTR, PCB is electrically complete for the first time
2022-09-01 Signal clatification in readme
2022-09-02 Add more schematic updates from Helen Croft
2022-09-02 Change to correct xtal footprint
2022-09-02 Clean up remaining footprints
2022-09-02 Final ISA connector
2022-09-02 Xtal Values
2022-09-03 Fix clearance issue between a via and a track
    Increased clearance between via "Net-(TP91-Pad1)" and track "Net-(TP57-Pad1)" (was 0.0975 mm) by moving it down slightly and adjusting traces.
2022-09-03 Remove all unconnected trace stubs
    Removed 9 unconnected trace stubs and cleaned up their parent traces where required.
2022-09-03 Replace GND ISA pin 1 polygon with filled zone
    Use of polygons for traces is strongly discouraged, they are intended for visual use only, replaced with filled zone. Adjusted trace slightly.
    To re-calculate all filled zones on a PCB press "b".
2022-09-03 Moved TestPoint REFDES to User Comments layer
    REFDES for TP72 on B.Silkscreen interferes with C9 pad, no TP markings appear on original PCB so changed TestPoint REFDES to User Comments layer, pushed to all 108 test points on PCB.
2022-09-03 Fix "Bracket Mount" footprint
    Changed "Bracket Mount" footprint to a proper pad instead of multiple polygons on layers and assigned pad to GND net.
    Added DRC exclusions for two GND traces going into bracket mount footprint (too close to NPTH).
2022-09-04 Update PDF and gerbers
2022-09-04 Added Card bracket with help from Helen Croft and updated main render
2022-09-04 Add images of different card revision
2022-09-04 Add missing files"
2022-09-05 Clean up SMD pad traces, change to hand solder pads to better match, and add missing models
2022-09-05 All traces increased to 0.4mm minimum
2022-09-05 Final cleanup complete
2022-09-05 Add attributtions
2022-09-05 Add cap values measured by Roland
2022-09-05 Adjust silk
2022-09-05 Updated readme, pdf, & gerbers
2022-09-05 Updated 3d render
2022-09-05 Spelling is hard
2022-09-08 minor trace cleanup
2022-09-08 Added some digikey parts
2022-09-08 fix table
2022-09-08 Add passives (and correct C2)
2022-09-09 Added mouser parts and card bracket
2022-09-09 fix readme
2022-09-10 Added new 3d work from Helen_Croft
2022-09-12 Final checks before production
2022-09-17 spelling
2022-10-09 Attempt to group functions logically for better readability
    Edited by Kicad 5, so the schematics and PCB have been upgraded
2022-10-12 Tweaks to the schematic
    Added explanation of circuit to project description
2022-10-12 Clarify 8215 operations
2022-11-13 Fix typo in readme

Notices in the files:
EDA/ISA-Card/ISA-Card.kicad_pcb:
Licensed under CERN-OHL-S: https://cern-ohl.web.cern.ch
